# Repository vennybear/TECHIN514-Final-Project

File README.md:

# Door Detective: Privacy-First Ambient Entry System

> **"A smart doorbell that hears the rhythm, not the person."**

**Door Detective** is a "Calm Technology" smart home solution designed to replace invasive cameras and distracting phone notifications. By using acoustic vibration sensing and temporal pattern analysis, it identifies visitors based on their knocking rhythm and provides a physical, non-intrusive notification on a desktop gauge.

---

## Hero Shot

---

## Core Concept
Most smart doorbells compromise domestic privacy by recording video and demanding constant attention through push notifications. 
**Door Detective solves this by:**
1. **Privacy-Preserving Sensing**: Using an accelerometer instead of a camera.
2. **Ambient Notification**: Using a physical needle and an analog gauge for "at-a-glance" awareness.
3. **Edge Intelligence**: Classifying visitors locally using vibration signatures.

---

## System Architecture
The system consists of two nodes communicating via the **ESP-NOW** protocol for ultra-low latency (<100ms) without the need for a router.

*   **Sensing Node (The "Ear")**: Mounted on the door. It captures high-frequency vibration data using an LIS3DH sensor and processes it on an ESP32 DevKit.
*   **Display Node (The "Face")**: Sits on the desk. A Seeed Studio XIAO ESP32C3 receives signals and actuates an X27 stepper motor to move the needle.

---

## Hardware Specifications

| Component | Category | Details |
| :--- | :--- | :--- |
| **MCU 1** | Sensing | ESP32 DevKit V1 |
| **MCU 2** | Display | Seeed Studio XIAO ESP32C3 |
| **Sensor** | Vibration | Adafruit LIS3DH (3-Axis Accelerometer) |
| **Actuator** | Motor | X27.168 Bipolar Stepper Motor |
| **Power** | Battery | 3.7V 1000mAh LiPo (Sensing Node) |
| **Interface** | Button | 16mm Latching Push Button |
| **Enclosure** | Manufacturing | Custom 3D-printed (Fusion 360) |

---

## Software & DSP Algorithm
To fulfill the machine learning/DSP requirements, I developed a **Temporal Feature Extraction** pipeline:

1. **Signal Magnitude Vector (SMV)**: Combines X, Y, and Z axes to normalize energy readings regardless of sensor orientation.
2. **Inter-Knock Interval (IKI) Analysis**: Measures the time between peaks to classify intent:
    *   **Urgent (Delivery)**: IKI < 500ms (Rapid double-tap) ➜ Needle points Left.
    *   **Social (Friend)**: IKI 500-1200ms (Rhythmic knock) ➜ Needle points Right.
    *   **General (Guest)**: Single tap / Timeout ➜ Needle points Center.

**Accuracy**: ~85% during internal validation testing.

---

## Hardware Iteration & Lessons Learned
This project was a journey of engineering resilience.
*   **PCB Rev 1.0 Fail**: A footprint pitch mismatch caused the ESP32 headers to be too narrow.
*   **Scrappy Prototyping**: Instead of waiting for a re-milling, I pivoted to a fly-wire assembly strategy to validate the I2C bus and electrical logic.
*   **Final Revision**: The sensing node now features a custom single-sided PCB with integrated pull-up resistors and optimized power traces.

---

## Power Management
*   **Strategy**: Implemented a software-based **Timed Light Sleep** mode (50ms cycles).
*   **Performance**: Reduced average idle current from 80mA to ~15mA, allowing the 1000mAh battery to last through long periods of monitoring.
*   **Future Work**: Routing the LIS3DH interrupt pin to enable true hardware Deep Sleep (uA levels).

---

## Repository Structure
*   `/src`: Firmware for both Sensing and Display nodes.
*   `/hardware`: KiCad schematics, PCB layout, and Gerber files.
*   `/cad`: Fusion 360 3D models (.f3d and .step).
*   `/docs`: Datasheets, Power calculation spreadsheet, and FMEA report.

---

## Author
**Yuna Xiong**
Technology Innovation (MSTI) Graduate Student at the University of Washington.

---

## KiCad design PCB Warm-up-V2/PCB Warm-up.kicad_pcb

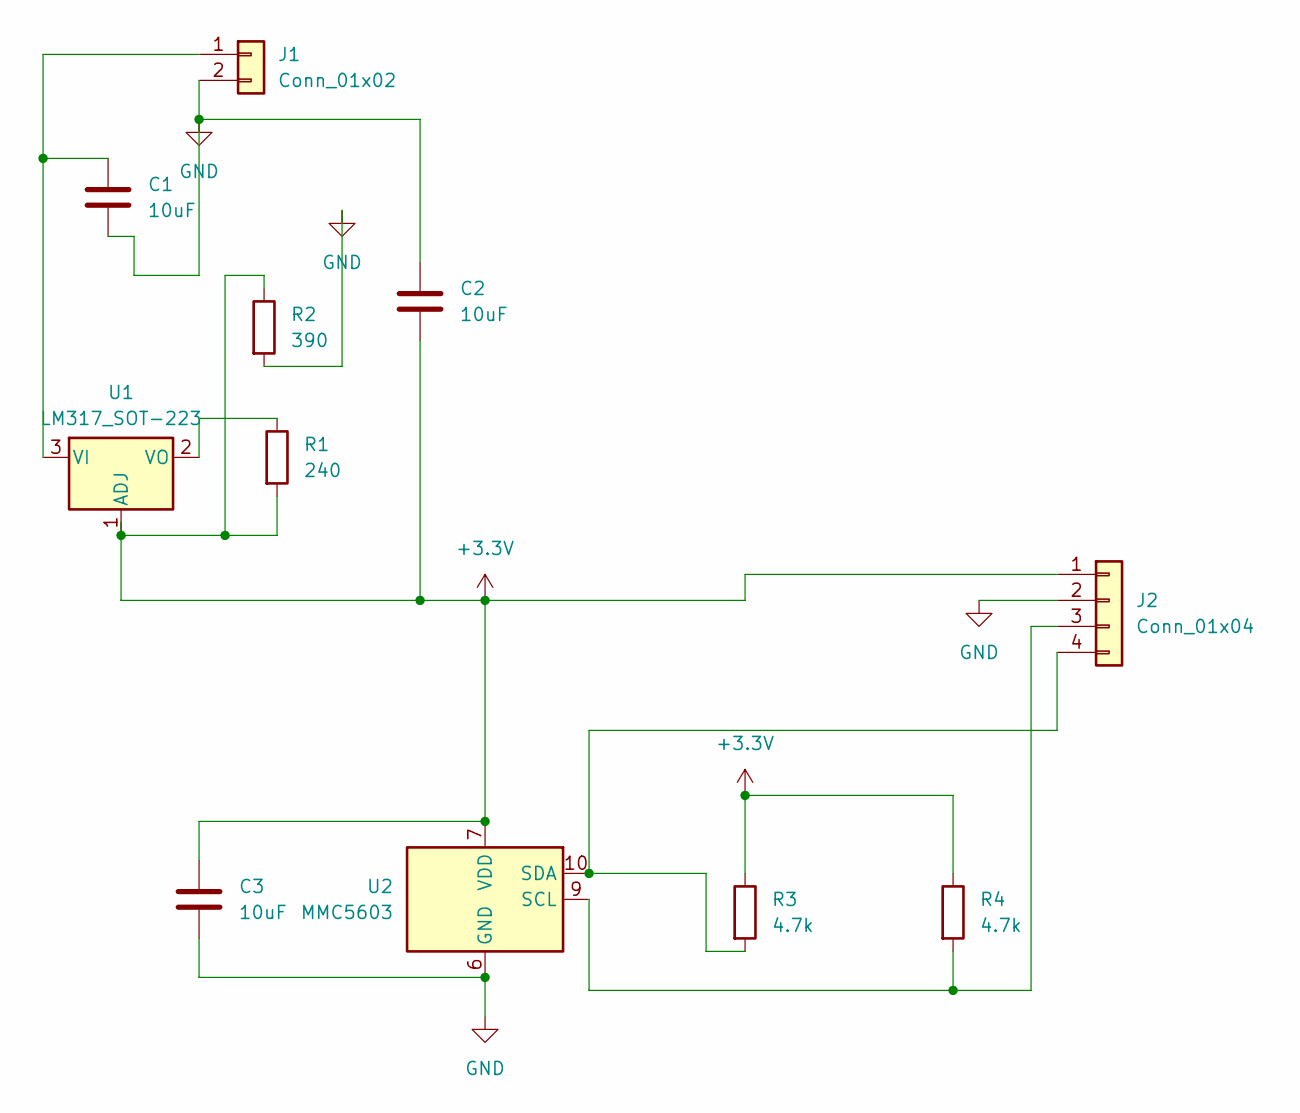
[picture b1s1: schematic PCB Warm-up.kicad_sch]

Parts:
C1, C2, C3: 10uF; C_0805_2012Metric
J1: Conn_01x02; PinHeader_1x02_P2.54mm_Vertical
J2: Conn_01x04; PinHeader_1x04_P2.54mm_Vertical
R1: 240; R_0805_2012Metric
R2: 390; R_0805_2012Metric
R3, R4: 4.7k; R_0805_2012Metric
U1: LM317_SOT-223; SOT-223-3_TabPin2
U2: MMC5603; Sensirion_SCD4x-1EP_10.1x10.1mm_P1.25mm_EP4.8x4.8mm

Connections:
+3.3V: C2.2, C3.1, J2.1, R1.2, R2.1, R3.1, R4.1, U1.1 (ADJ), U2.7 (VDD), U2.19 (VDD)
GND: C1.2, C2.1, C3.2, J1.2, J2.2, R2.2, U2.6 (GND), U2.20 (GND), U2.21 (GND)
unnamed: C1.1, J1.1, U1.3 (VI)
unnamed: J2.3, R4.2, U2.9 (SCL)
unnamed: J2.4, R3.2, U2.10 (SDA)
unnamed: R1.1, U1.2 (VO)

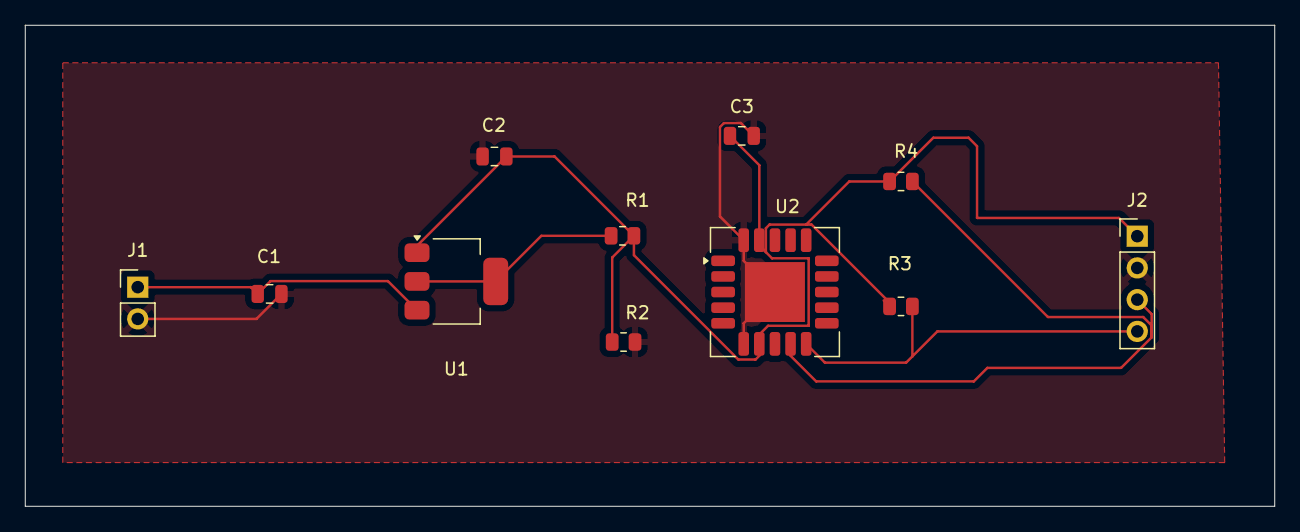
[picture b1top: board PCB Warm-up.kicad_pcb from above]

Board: 2 copper layers, 100.0 x 38.5 mm, 11 parts (0 on the bottom side), 6 nets.

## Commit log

2026-01-20 README.md
2026-01-30 Rename f22cebc4fa65dc76c38133afc52b35b3.png to PCB.png
2026-03-16 Create scr
